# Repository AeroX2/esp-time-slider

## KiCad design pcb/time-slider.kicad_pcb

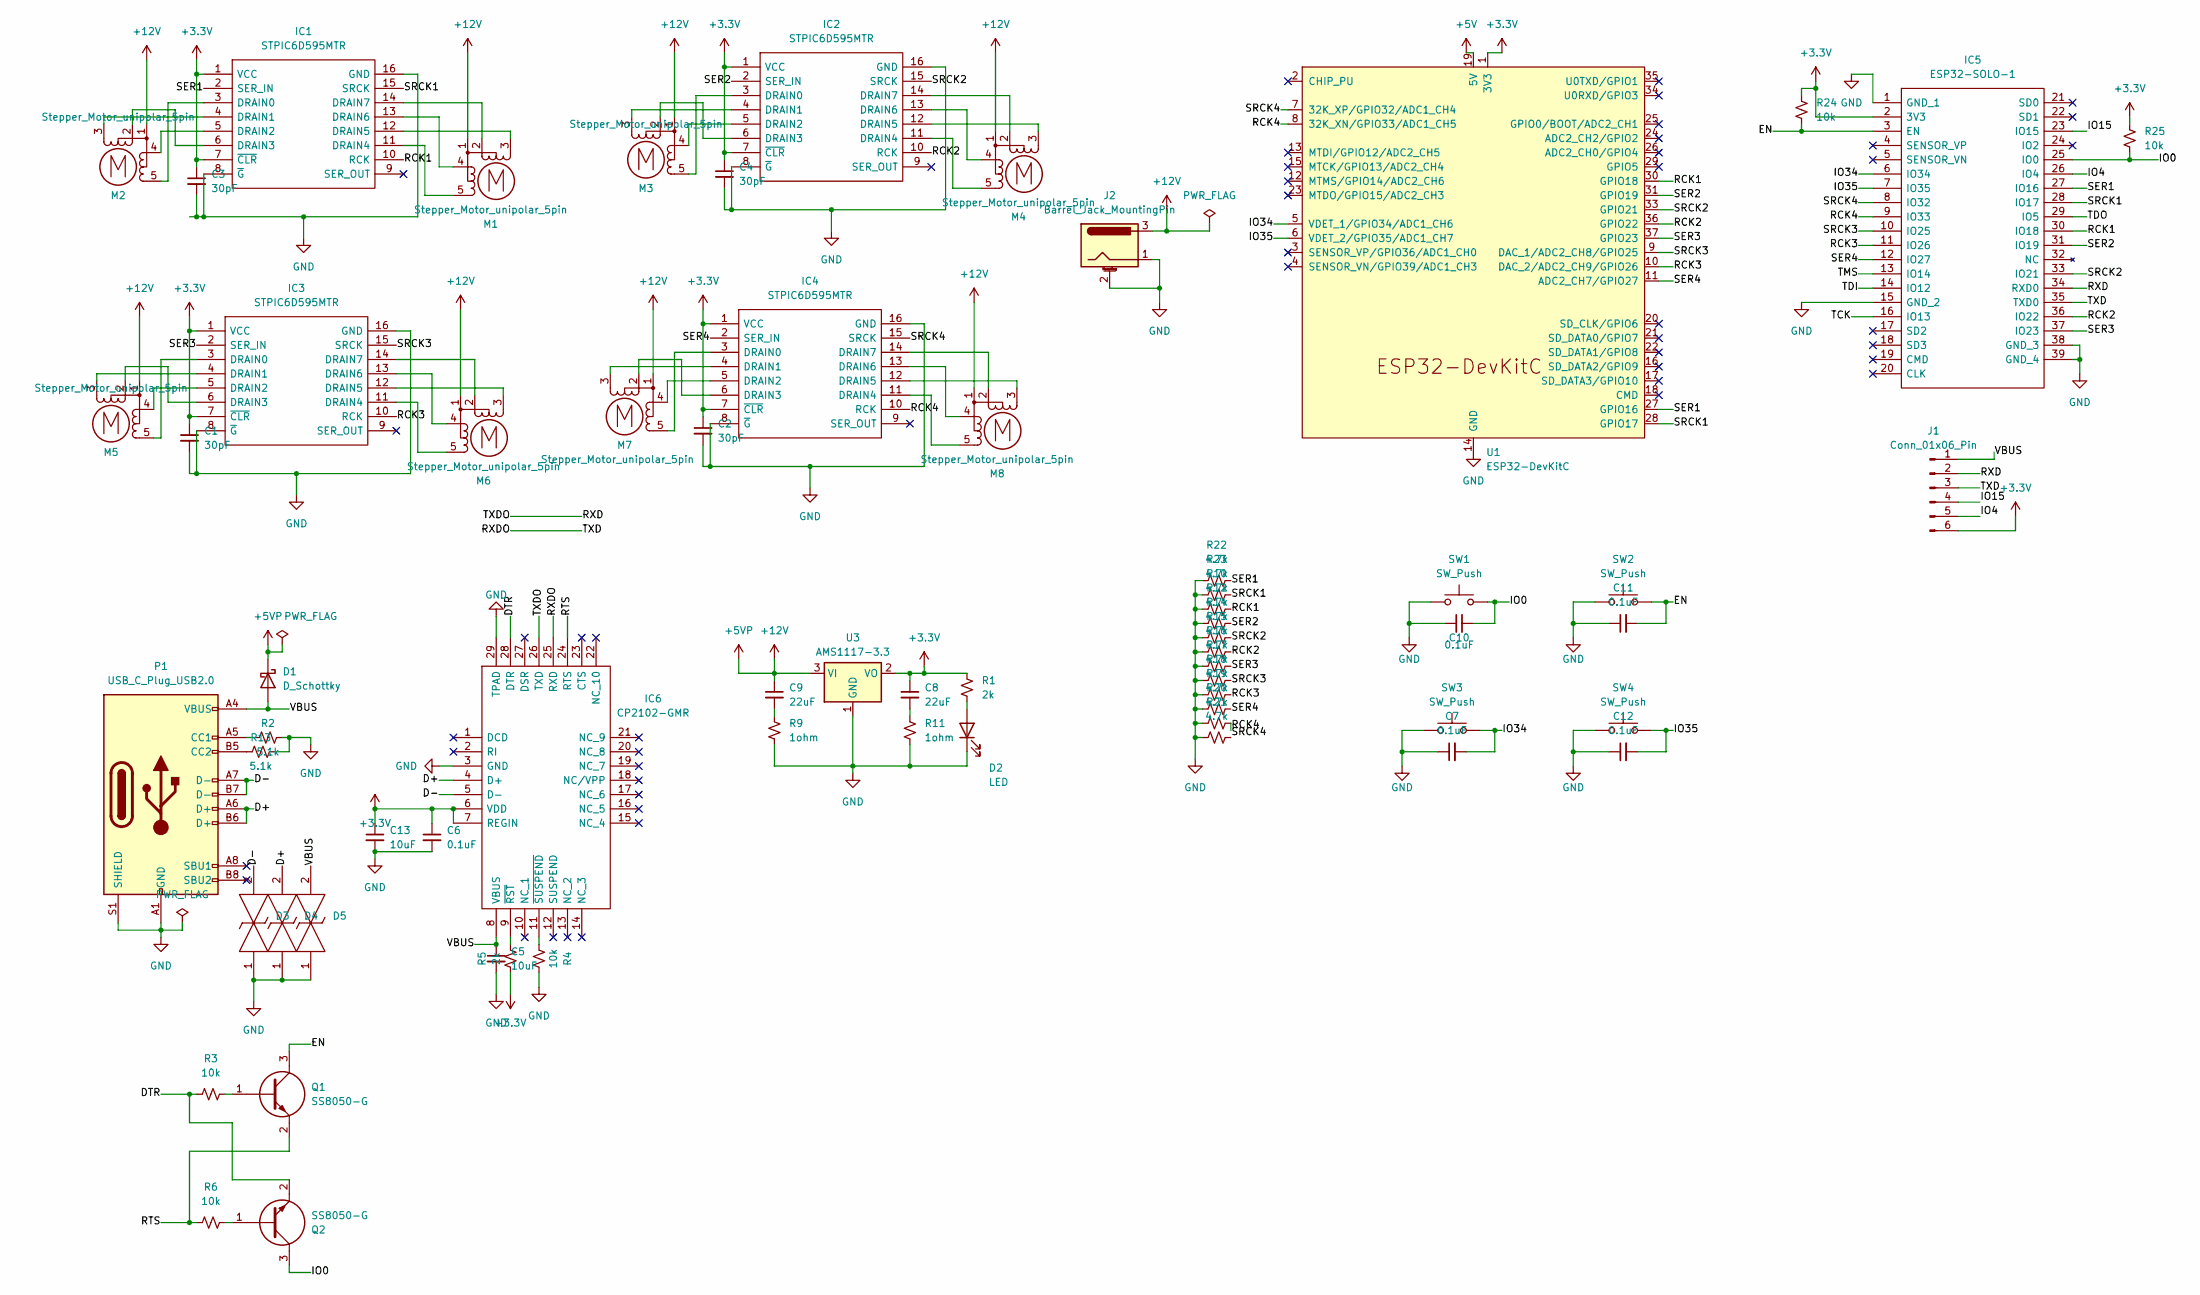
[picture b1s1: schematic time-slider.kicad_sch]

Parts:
C1, C2, C3, C4: 30pF; C_0402_1005Metric
C5, C13: 10uF; C_0402_1005Metric
C6, C7, C10, C11, C12: 0.1uF; C_0402_1005Metric
C8, C9: 22uF; C_0603_1608Metric
D1: D_Schottky; D_SOD-323; LCSC C191023
D2: LED; LED_0603_1608Metric
D3, D4, D5: LESD5D5.0CT1G; LESD5D50CT1G; Manufacturer_Part_Number LESD5D5.0CT1G; LCSC C383211
IC1, IC2, IC3, IC4: STPIC6D595MTR; SOIC127P600X175-16N; Manufacturer_Part_Number STPIC6D595MTR; Mouser Part Number 511-STPIC6D595MTR
IC5: ESP32-SOLO-1; ESP32SOLO1; Manufacturer_Part_Number ESP32-SOLO-1; Mouser Part Number 356-ESP32-SOLO-1
IC6: CP2102-GMR; QFN50P500X500X100-29N-D; Manufacturer_Part_Number CP2102-GMR; Mouser Part Number 634-CP2102-GMR
J1: Conn_01x06_Pin; PinHeader_2x03_P2.54mm_Vertical
J2: Barrel_Jack_MountingPin; DC00525A25; LCSC C319098
M1, M2, M3, M4, M5, M6, M7, M8: Stepper_Motor_unipolar_5pin; JST_XH_B5B-XH-A_1x05_P2.50mm_Vertical; LCSC C2318
P1: USB_C_Plug_USB2.0; USB-C-SMD_KH-TYPE-C-16P
Q1, Q2: SS8050-G; SOT95P240X115-3N; Manufacturer_Part_Number SS8050-G; Mouser Part Number 750-SS8050-G
R1, R5: 2k; R_0402_1005Metric
R2, R13: 5.1k; R_0402_1005Metric
R3, R4, R6, R24, R25: 10k; R_0402_1005Metric
R9, R11: 1ohm; R_0805_2012Metric
R10, R12, R14, R15, R16, R17, R18, R19, R20, R21, R22, R23: 4.7k; R_0402_1005Metric
SW1, SW2, SW3, SW4: SW_Push; TS1187ABAB; LCSC C318884
U1: ESP32-DevKitC
U3: AMS1117-3.3; SOT-223-3_TabPin2

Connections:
+3.3V: C1.1, C2.1, C3.1, C4.1, C6.1, C8.1, C13.1, IC1.1 (VCC), IC1.7 (~CLR), IC2.1 (VCC), IC2.7 (~CLR), IC3.1 (VCC), IC3.7 (~CLR), IC4.1 (VCC), IC4.7 (~CLR), IC5.2 (3V3), IC6.6 (VDD), IC6.7 (REGIN), J1.6, R1.1, R5.1, R24.1, R25.2, U1.1 (3V3), U3.2 (VO)
+5V: U1.19 (5V)
+12V: C9.1, D1.1 (K), J2.3, M1.1, M2.1, M3.1, M4.1, M5.1, M6.1, M7.1, M8.1, U3.3 (VI)
/D+: D4.2, IC6.4 (D+), P1.A6 (D+), P1.B6 (D+)
/D-: D3.2, IC6.5 (D-), P1.A7 (D-), P1.B7 (D-)
/DTR: IC6.28 (DTR), Q2.2, R3.1
/EN: C11.2, IC5.3 (EN), Q1.3, R24.2, SW2.2
/IO0: C10.2, IC5.25 (IO0), Q2.3, R25.1, SW1.2
/IO4: IC5.26 (IO4), J1.5
/IO15: IC5.23 (IO15), J1.4
/IO34: C7.2, IC5.6 (IO34), SW3.2, U1.5 (VDET_1/GPIO34/ADC1_CH6)
/IO35: C12.2, IC5.7 (IO35), SW4.2, U1.6 (VDET_2/GPIO35/ADC1_CH7)
/RCK1: IC1.10 (RCK), IC5.30 (IO18), R10.2, U1.30 (GPIO18)
/RCK2: IC2.10 (RCK), IC5.36 (IO22), R15.2, U1.36 (GPIO22)
/RCK3: IC3.10 (RCK), IC5.11 (IO26), R18.2, U1.10 (DAC_2/ADC2_CH9/GPIO26)
/RCK4: IC4.10 (RCK), IC5.9 (IO33), R20.2, U1.8 (32K_XN/GPIO33/ADC1_CH5)
/RTS: IC6.24 (RTS), Q1.2, R6.1
/RXD: IC5.34 (RXD0), IC6.26 (TXD), J1.2
/RXDO: IC5.35 (TXD0), IC6.25 (RXD), J1.3
/SER1: IC1.2 (SER_IN), IC5.27 (IO16), R22.2, U1.27 (GPIO16)
/SER2: IC2.2 (SER_IN), IC5.31 (IO19), R12.2, U1.31 (GPIO19)
/SER3: IC3.2 (SER_IN), IC5.37 (IO23), R16.2, U1.37 (GPIO23)
/SER4: IC4.2 (SER_IN), IC5.12 (IO27), R19.2, U1.11 (ADC2_CH7/GPIO27)
/SRCK1: IC1.15 (SRCK), IC5.28 (IO17), R23.2, U1.28 (GPIO17)
/SRCK2: IC2.15 (SRCK), IC5.33 (IO21), R14.2, U1.33 (GPIO21)
/SRCK3: IC3.15 (SRCK), IC5.10 (IO25), R17.2, U1.9 (DAC_1/ADC2_CH8/GPIO25)
/SRCK4: IC4.15 (SRCK), IC5.8 (IO32), R21.2, U1.7 (32K_XP/GPIO32/ADC1_CH4)
/TCK: IC5.16 (IO13)
/TDI: IC5.14 (IO12)
/TDO: IC5.29 (IO5)
/TMS: IC5.13 (IO14)
/VBUS: C5.1, D1.2 (A), D5.2, IC6.8 (VBUS), J1.1, P1.A4 (VBUS), P1.A9 (VBUS), P1.B4 (VBUS), P1.B9 (VBUS)
GND: C1.2, C2.2, C3.2, C4.2, C5.2, C6.2, C7.1, C10.1, C11.1, C12.1, C13.2, D2.1 (K), D3.1, D4.1, D5.1, IC1.8 (~G), IC1.16 (GND), IC2.8 (~G), IC2.16 (GND), IC3.8 (~G), IC3.16 (GND), IC4.8 (~G), IC4.16 (GND), IC5.1 (GND_1), IC5.15 (GND_2), IC5.38 (GND_3), IC5.39 (GND_4), IC6.3 (GND), IC6.29 (TPAD), J2.1, J2.2 (MountPin), P1.A1 (GND), P1.A12 (GND), P1.B1 (GND), P1.B12 (GND), P1.S1 (SHIELD), R2.1, R4.1, R9.2, R10.1, R11.2, R12.1, R13.1, R14.1, R15.1, R16.1, R17.1, R18.1, R19.1, R20.1, R21.1, R22.1, R23.1, SW1.1, SW2.1, SW3.1, SW4.1, U1.14 (GND), U1.32 (GND), U1.38 (GND), U3.1 (GND)
unnamed: C8.2, R11.1
unnamed: C9.2, R9.1
unnamed: D2.2 (A), R1.2
unnamed: IC1.3 (DRAIN0), M2.5
unnamed: IC1.4 (DRAIN1), M2.3 (-)
unnamed: IC1.5 (DRAIN2), M2.4
unnamed: IC1.6 (DRAIN3), M2.2
unnamed: IC1.11 (DRAIN4), M1.5
unnamed: IC1.12 (DRAIN5), M1.3 (-)
unnamed: IC1.13 (DRAIN6), M1.4
unnamed: IC1.14 (DRAIN7), M1.2
unnamed: IC2.3 (DRAIN0), M3.5
unnamed: IC2.4 (DRAIN1), M3.3 (-)
unnamed: IC2.5 (DRAIN2), M3.4
unnamed: IC2.6 (DRAIN3), M3.2
unnamed: IC2.11 (DRAIN4), M4.5
unnamed: IC2.12 (DRAIN5), M4.3 (-)
unnamed: IC2.13 (DRAIN6), M4.4
unnamed: IC2.14 (DRAIN7), M4.2
unnamed: IC3.3 (DRAIN0), M5.5
unnamed: IC3.4 (DRAIN1), M5.3 (-)
unnamed: IC3.5 (DRAIN2), M5.4
unnamed: IC3.6 (DRAIN3), M5.2
unnamed: IC3.11 (DRAIN4), M6.5
unnamed: IC3.12 (DRAIN5), M6.3 (-)
unnamed: IC3.13 (DRAIN6), M6.4
unnamed: IC3.14 (DRAIN7), M6.2
unnamed: IC4.3 (DRAIN0), M7.5
unnamed: IC4.4 (DRAIN1), M7.3 (-)
unnamed: IC4.5 (DRAIN2), M7.4
unnamed: IC4.6 (DRAIN3), M7.2
unnamed: IC4.11 (DRAIN4), M8.5
unnamed: IC4.12 (DRAIN5), M8.3 (-)
unnamed: IC4.13 (DRAIN6), M8.4
unnamed: IC4.14 (DRAIN7), M8.2
unnamed: IC6.9 (~RST), R5.2
unnamed: IC6.11 (~SUSPEND), R4.2
unnamed: P1.A5 (CC1), R2.2
unnamed: P1.B5 (CC2), R13.2
unnamed: Q1.1, R3.2
unnamed: Q2.1, R6.2

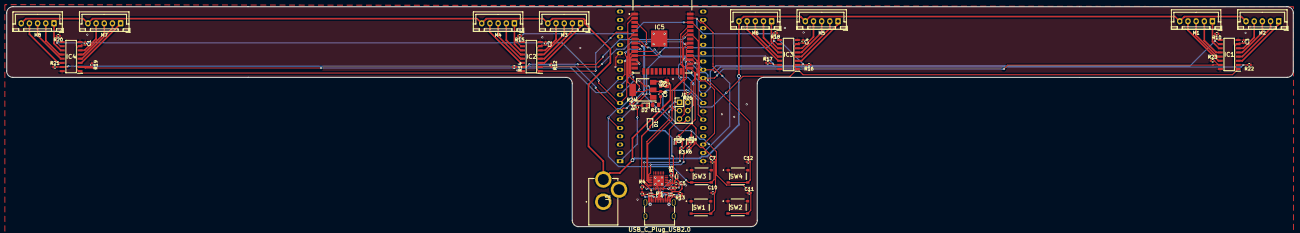
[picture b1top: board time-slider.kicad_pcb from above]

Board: 2 copper layers, 393.1 x 67.2 mm, 66 parts (1 on the bottom side), 69 nets.

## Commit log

2023-08-30 Attempt to talk with motor drivers
2024-05-01 Everything should be working
